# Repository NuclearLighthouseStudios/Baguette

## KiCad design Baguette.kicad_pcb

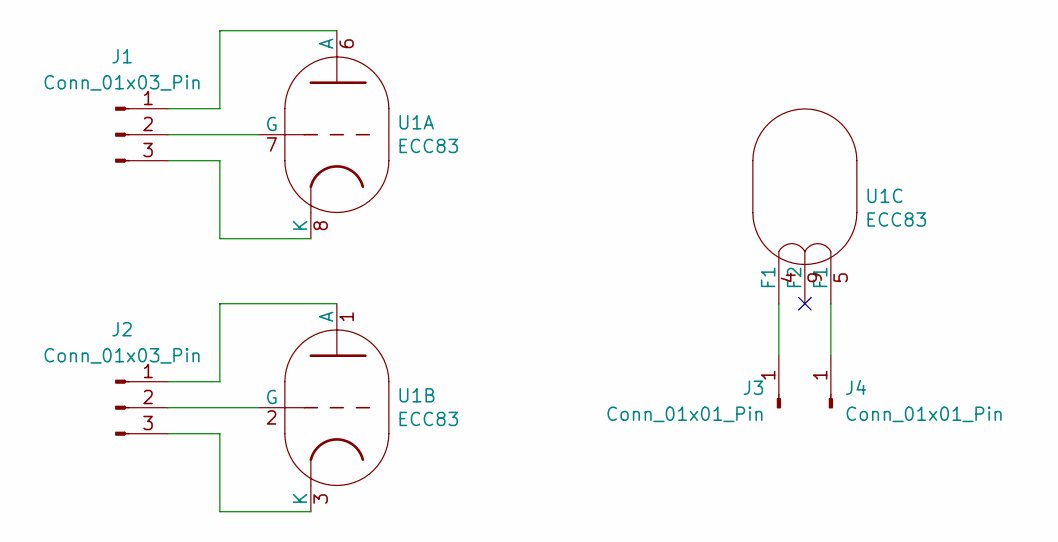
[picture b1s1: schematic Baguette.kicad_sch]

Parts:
J1, J2: Conn_01x03_Pin; PinHeader_1x03_P2.54mm_Vertical
J3, J4: Conn_01x01_Pin; PinHeader_1x01_P2.54mm_Vertical
U1: ECC83; VALVE-NOVAL_P

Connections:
unnamed: J1.1, U1.6 (A)
unnamed: J1.2, U1.7 (G)
unnamed: J1.3, U1.8 (K)
unnamed: J2.1, U1.1 (A)
unnamed: J2.2, U1.2 (G)
unnamed: J2.3, U1.3 (K)
unnamed: J3.1, U1.4 (F1)
unnamed: J4.1, U1.5 (F1)

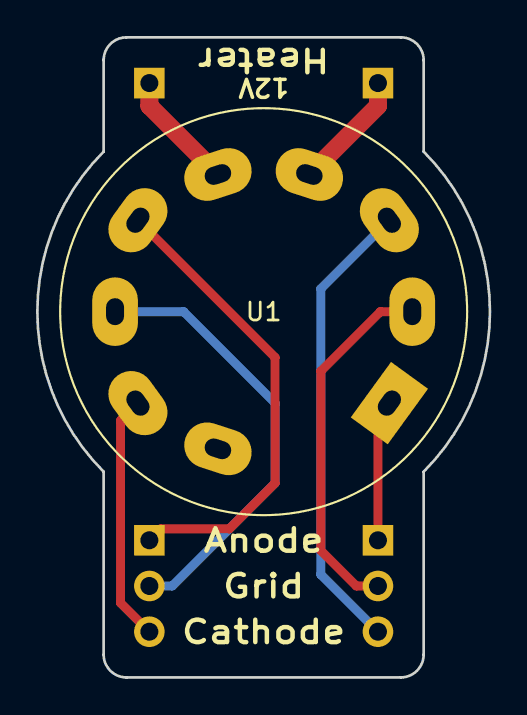
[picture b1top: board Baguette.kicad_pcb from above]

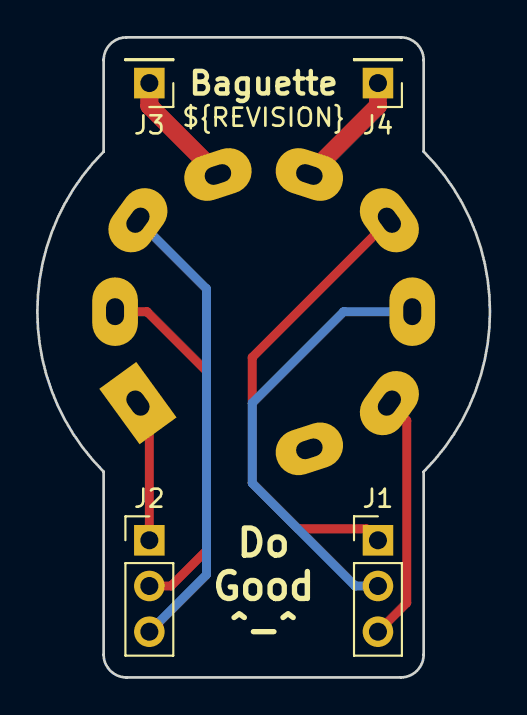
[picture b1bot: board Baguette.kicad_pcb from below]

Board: 2 copper layers, 25.1 x 35.6 mm, 5 parts (4 on the bottom side), 8 nets.

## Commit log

2020-02-23 Add LICENSE and some other missing stuff
2023-11-03 Update to latest KiCAD version
2023-11-03 Small updates

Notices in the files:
parts and their libraries:
LICENSE: CC BY-SA
